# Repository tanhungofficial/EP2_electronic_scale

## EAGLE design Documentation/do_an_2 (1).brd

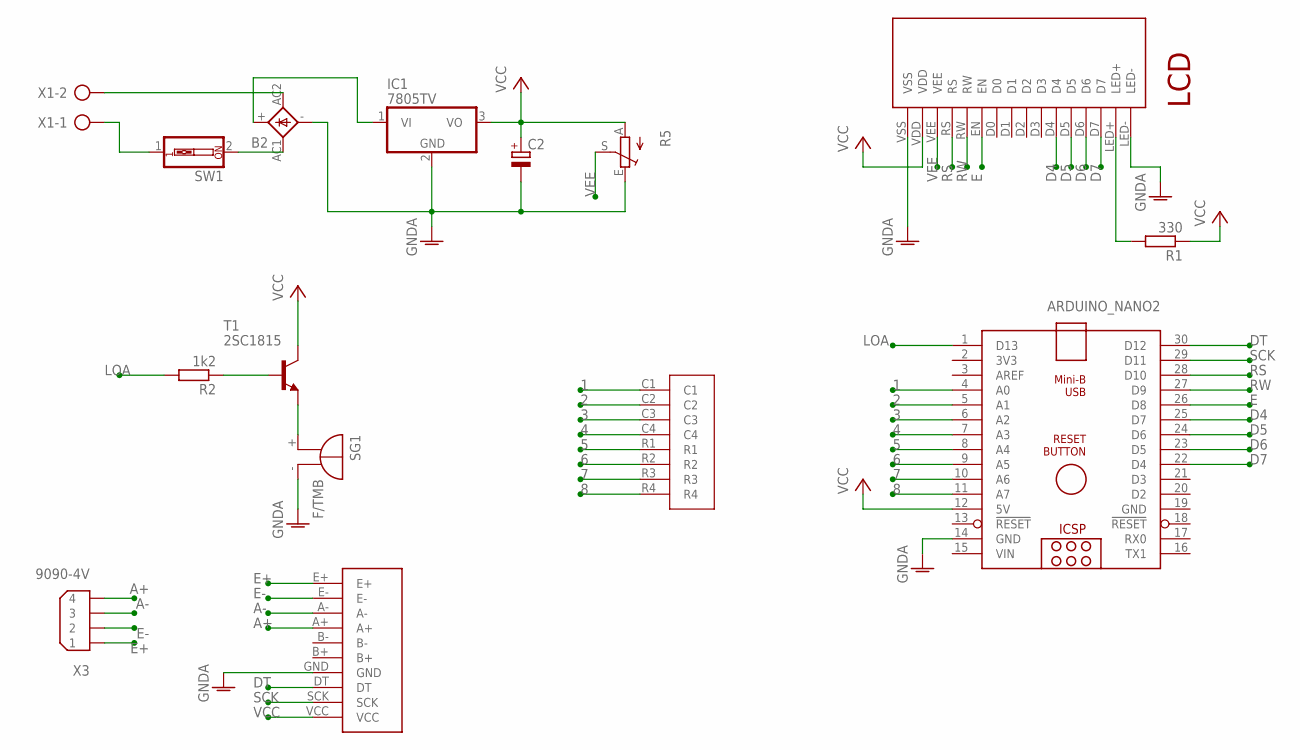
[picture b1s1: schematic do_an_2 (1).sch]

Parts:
ARDUINO_NANO2: ARDUINO_NANO
B2: 2KBP
C2: CPOL-EUE5-10.5; E5-10,5
IC1: 7805TV; TO220V
R1: 330; 0207/10
R2: 1k2; 0207/10
R5: TRIM_EU-S64W; S64W
SG1: F/TMB
SW1: SW_DIP-1; EDG-01
T1: 2SC1815; TO92-ECB
U$1: LCD20X4
U$2: MA_TRAN_PHIM
U$3: MACHMAUXANH
X1: AK300/2
X3: 9090-4V

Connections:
1: ARDUINO_NANO2.4 (A0), U$2.C1
2: ARDUINO_NANO2.5 (A1), U$2.C2
3: ARDUINO_NANO2.6 (A2), U$2.C3
4: ARDUINO_NANO2.7 (A3), U$2.C4
5: ARDUINO_NANO2.8 (A4), U$2.R1
6: ARDUINO_NANO2.9 (A5), U$2.R2
7: ARDUINO_NANO2.10 (A6), U$2.R3
8: ARDUINO_NANO2.11 (A7), U$2.R4
A+: U$3.A+, X3.4
A-: U$3.A-, X3.3
D4: ARDUINO_NANO2.25 (D7), U$1.D4
D5: ARDUINO_NANO2.24 (D6), U$1.D5
D6: ARDUINO_NANO2.23 (D5), U$1.D6
D7: ARDUINO_NANO2.22 (D4), U$1.D7
DT: ARDUINO_NANO2.30 (D12), U$3.DT
E: ARDUINO_NANO2.26 (D8), U$1.EN
E+: U$3.E+, X3.1
E-: U$3.E-, X3.2
GND: ARDUINO_NANO2.19 (GND)
GNDA: ARDUINO_NANO2.14 (GND), B2.-, C2.-, IC1.2 (GND), R5.E, SG1.-, U$1.LED-, U$1.VSS, U$3.GND
LOA: ARDUINO_NANO2.1 (D13), R2.2
unnamed: R2.1, T1.B
unnamed: B2.AC2, X1.2
unnamed: B2.AC1, SW1.2
unnamed: B2.+, IC1.1 (VI)
unnamed: R1.2, U$1.LED+
unnamed: SG1.+, T1.E
unnamed: SW1.1, X1.1
RS: ARDUINO_NANO2.28 (D10), U$1.RS
RW: ARDUINO_NANO2.27 (D9), U$1.RW
SCK: ARDUINO_NANO2.29 (D11), U$3.SCK
VCC: ARDUINO_NANO2.12 (5V), C2.+, IC1.3 (VO), R1.1, R5.A, T1.C, U$1.VDD, U$3.VCC
VEE: R5.S, U$1.VEE
VIN: ARDUINO_NANO2.15 (VIN)

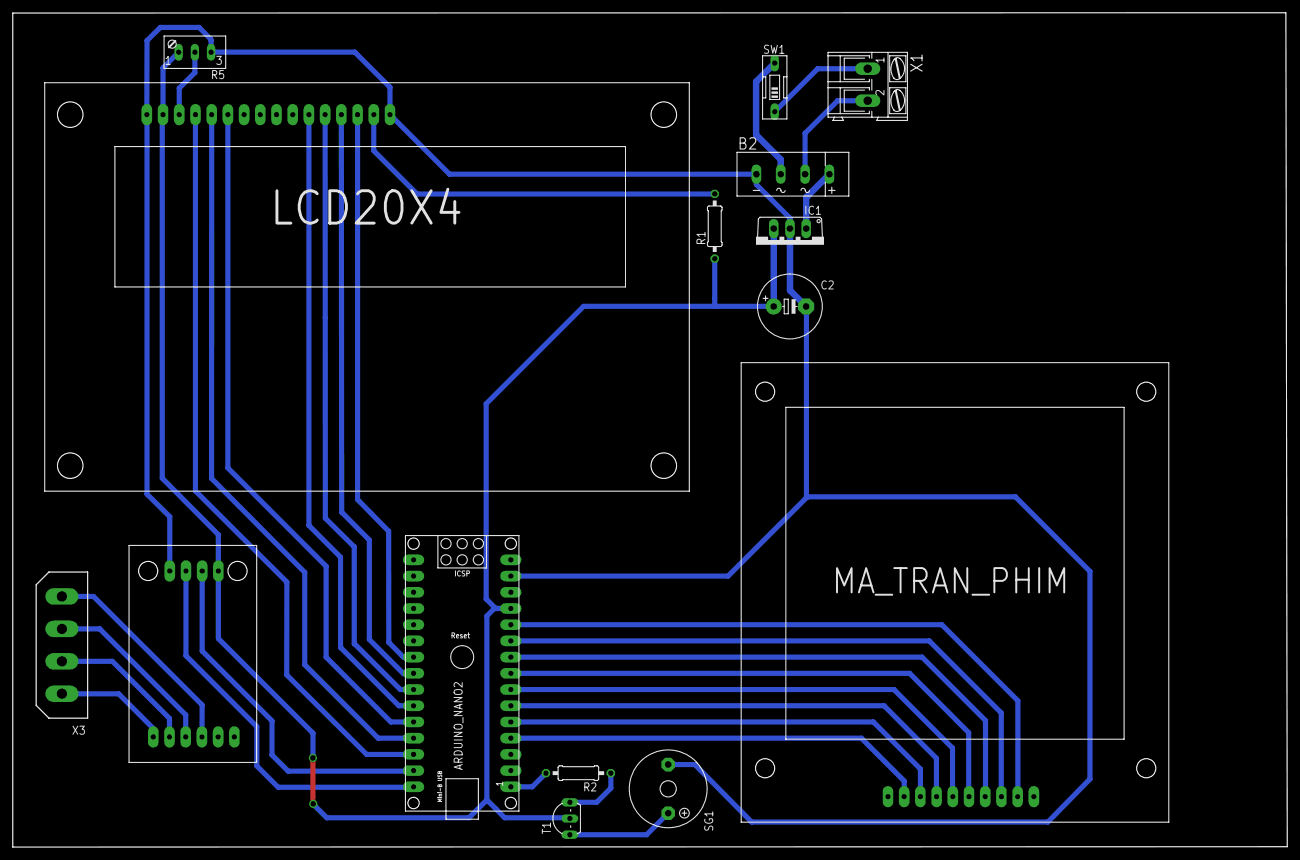
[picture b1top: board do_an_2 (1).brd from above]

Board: 2 copper layers, 199.7 x 130.7 mm, 15 parts (0 on the bottom side), 32 nets.

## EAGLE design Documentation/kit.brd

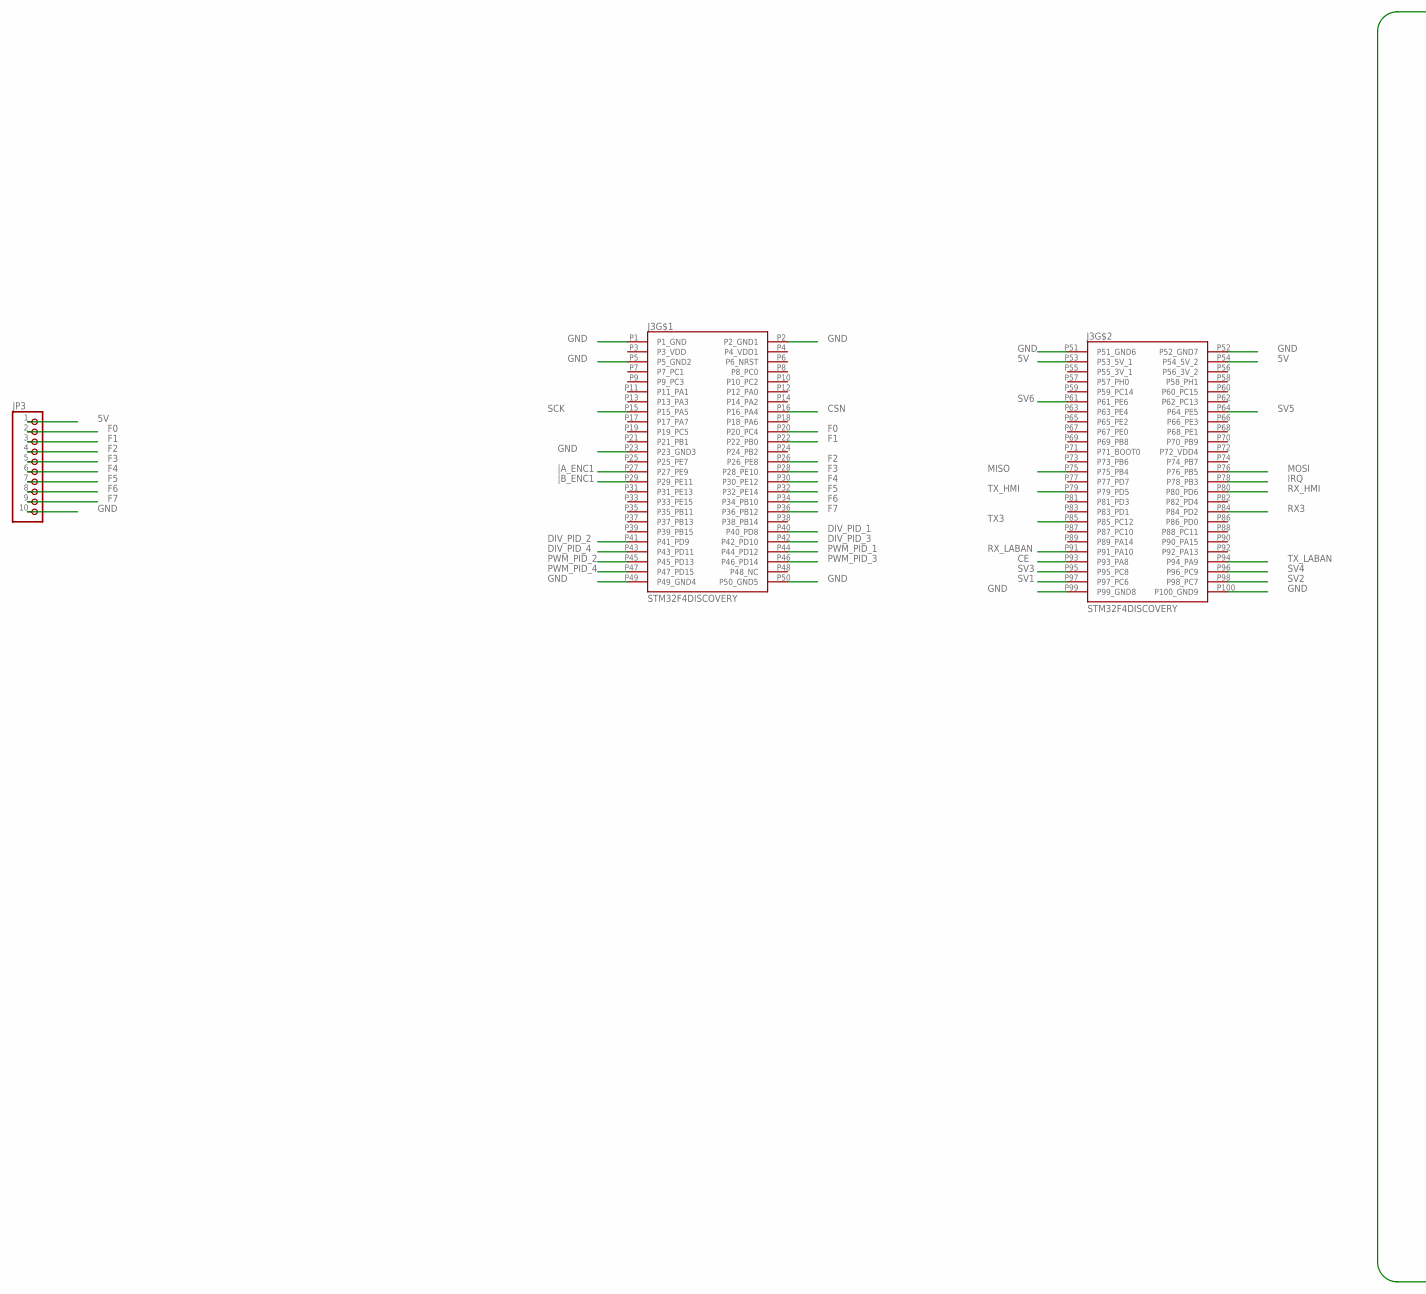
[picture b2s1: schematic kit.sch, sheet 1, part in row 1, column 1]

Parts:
J3: STM32F4DISCOVERY; STMICROELECTRONICS_STM32F4DISCOVERY
JP3: PINHD-1X10/90; 1X10/90

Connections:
5V: J3.P53 (P53_5V_1), J3.P54 (P54_5V_2), JP3.1; also elsewhere on the board
CE: J3.P93 (P93_PA8); also elsewhere on the board
CSN: J3.P16 (P16_PA4); also elsewhere on the board
DIV_PID_1: J3.P40 (P40_PD8); also elsewhere on the board
DIV_PID_2: J3.P41 (P41_PD9); also elsewhere on the board
DIV_PID_3: J3.P42 (P42_PD10); also elsewhere on the board
DIV_PID_4: J3.P43 (P43_PD11); also elsewhere on the board
F0: J3.P20 (P20_PC4), JP3.2
F1: J3.P22 (P22_PB0), JP3.3
F2: J3.P26 (P26_PE8), JP3.4
F3: J3.P28 (P28_PE10), JP3.5
F4: J3.P30 (P30_PE12), JP3.6
F5: J3.P32 (P32_PE14), JP3.7
F6: J3.P34 (P34_PB10), JP3.8
F7: J3.P36 (P36_PB12), JP3.9
GND: J3.P1 (P1_GND), J3.P2 (P2_GND1), J3.P5 (P5_GND2), J3.P23 (P23_GND3), J3.P49 (P49_GND4), J3.P50 (P50_GND5), J3.P51 (P51_GND6), J3.P52 (P52_GND7), J3.P99 (P99_GND8), J3.P100 (P100_GND9), JP3.10; also elsewhere on the board
IRQ: J3.P78 (P78_PB3); also elsewhere on the board
MISO: J3.P75 (P75_PB4); also elsewhere on the board
MOSI: J3.P76 (P76_PB5); also elsewhere on the board
PWM_PID_1: J3.P44 (P44_PD12); also elsewhere on the board
PWM_PID_2: J3.P45 (P45_PD13); also elsewhere on the board
PWM_PID_3: J3.P46 (P46_PD14); also elsewhere on the board
PWM_PID_4: J3.P47 (P47_PD15); also elsewhere on the board
RX3: J3.P84 (P84_PD2); also elsewhere on the board
RX_HMI: J3.P80 (P80_PD6)
RX_LABAN: J3.P91 (P91_PA10); also elsewhere on the board
SCK: J3.P15 (P15_PA5); also elsewhere on the board
SV1: J3.P97 (P97_PC6); also elsewhere on the board
SV2: J3.P98 (P98_PC7); also elsewhere on the board
SV3: J3.P95 (P95_PC8); also elsewhere on the board
SV4: J3.P96 (P96_PC9); also elsewhere on the board
SV5: J3.P64 (P64_PE5)
SV6: J3.P61 (P61_PE6)
TX3: J3.P85 (P85_PC12); also elsewhere on the board
TX_HMI: J3.P79 (P79_PD5)
TX_LABAN: J3.P94 (P94_PA9); also elsewhere on the board
|A_ENC1: J3.P27 (P27_PE9); also elsewhere on the board
|B_ENC1: J3.P29 (P29_PE11); also elsewhere on the board

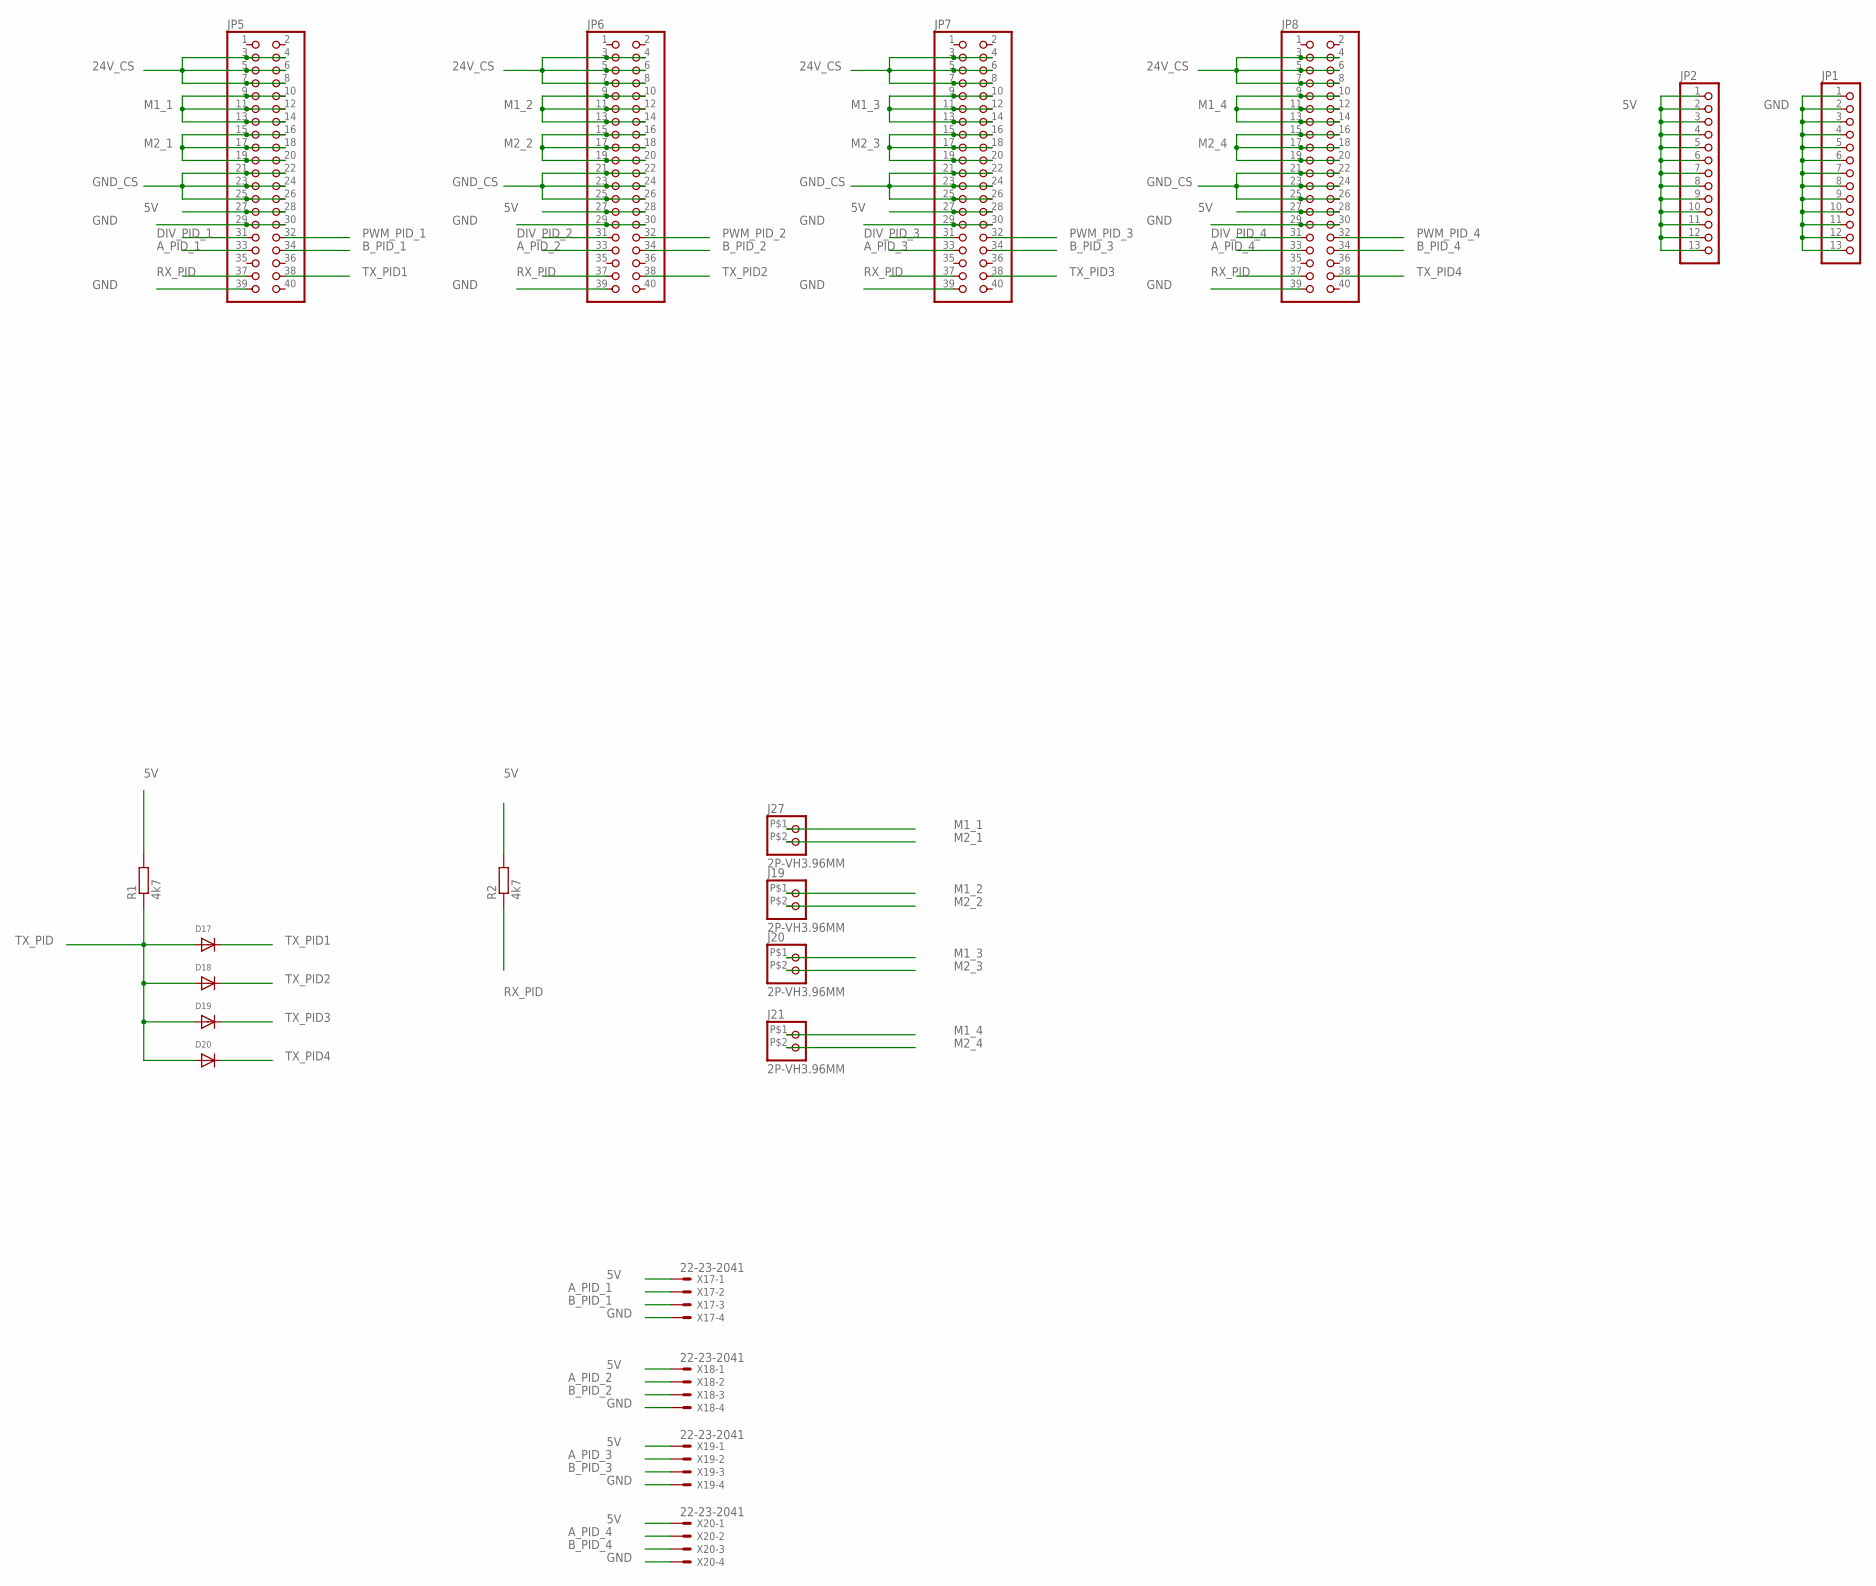
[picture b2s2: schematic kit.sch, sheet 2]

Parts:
D17, D18, D19, D20: DIODEDO-1N4148; DO-1N4148
J19, J20, J21, J27: 2P-VH3.96MM
JP1, JP2: PINHD-1X13; 1X13
JP5, JP6, JP7, JP8: PINHD-2X20; 2X20
R1, R2: 4k7; 0207/10
X17, X18, X19, X20: 22-23-2041

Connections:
5V: JP2.1, JP2.2, JP2.3, JP2.4, JP2.5, JP2.6, JP2.7, JP2.8, JP2.9, JP2.10, JP2.11, JP2.12, JP2.13, JP5.27, JP5.28, JP6.27, JP6.28, JP7.27, JP7.28, JP8.27, JP8.28, R1.2, R2.2, X17.1, X18.1, X19.1, X20.1; also elsewhere on the board
24V_CS: JP5.3, JP5.4, JP5.5, JP5.6, JP5.7, JP5.8, JP6.3, JP6.4, JP6.5, JP6.6, JP6.7, JP6.8, JP7.3, JP7.4, JP7.5, JP7.6, JP7.7, JP7.8, JP8.3, JP8.4, JP8.5, JP8.6, JP8.7, JP8.8; also elsewhere on the board
A_PID_1: JP5.33, X17.2
A_PID_2: JP6.33, X18.2
A_PID_3: JP7.33, X19.2
A_PID_4: JP8.33, X20.2
B_PID_1: JP5.34, X17.3
B_PID_2: JP6.34, X18.3
B_PID_3: JP7.34, X19.3
B_PID_4: JP8.34, X20.3
DIV_PID_1: JP5.31; also elsewhere on the board
DIV_PID_2: JP6.31; also elsewhere on the board
DIV_PID_3: JP7.31; also elsewhere on the board
DIV_PID_4: JP8.31; also elsewhere on the board
GND: JP1.1, JP1.2, JP1.3, JP1.4, JP1.5, JP1.6, JP1.7, JP1.8, JP1.9, JP1.10, JP1.11, JP1.12, JP1.13, JP5.29, JP5.30, JP5.39, JP6.29, JP6.30, JP6.39, JP7.29, JP7.30, JP7.39, JP8.29, JP8.30, JP8.39, X17.4, X18.4, X19.4, X20.4; also elsewhere on the board
GND_CS: JP5.21, JP5.22, JP5.23, JP5.24, JP5.25, JP5.26, JP6.21, JP6.22, JP6.23, JP6.24, JP6.25, JP6.26, JP7.21, JP7.22, JP7.23, JP7.24, JP7.25, JP7.26, JP8.21, JP8.22, JP8.23, JP8.24, JP8.25, JP8.26; also elsewhere on the board
M1_1: J27.P$1 (1), JP5.9, JP5.10, JP5.11, JP5.12, JP5.13, JP5.14
M1_2: J19.P$1 (1), JP6.9, JP6.10, JP6.11, JP6.12, JP6.13, JP6.14
M1_3: J20.P$1 (1), JP7.9, JP7.10, JP7.11, JP7.12, JP7.13, JP7.14
M1_4: J21.P$1 (1), JP8.9, JP8.10, JP8.11, JP8.12, JP8.13, JP8.14
M2_1: J27.P$2 (2), JP5.15, JP5.16, JP5.17, JP5.18, JP5.19, JP5.20
M2_2: J19.P$2 (2), JP6.15, JP6.16, JP6.17, JP6.18, JP6.19, JP6.20
M2_3: J20.P$2 (2), JP7.15, JP7.16, JP7.17, JP7.18, JP7.19, JP7.20
M2_4: J21.P$2 (2), JP8.15, JP8.16, JP8.17, JP8.18, JP8.19, JP8.20
PWM_PID_1: JP5.32; also elsewhere on the board
PWM_PID_2: JP6.32; also elsewhere on the board
PWM_PID_3: JP7.32; also elsewhere on the board
PWM_PID_4: JP8.32; also elsewhere on the board
RX_PID: JP5.37, JP6.37, JP7.37, JP8.37, R2.1; also elsewhere on the board
TX_PID: D17.A, D18.A, D19.A, D20.A, R1.1; also elsewhere on the board
TX_PID1: D17.C, JP5.38
TX_PID2: D18.C, JP6.38
TX_PID3: D19.C, JP7.38
TX_PID4: D20.C, JP8.38

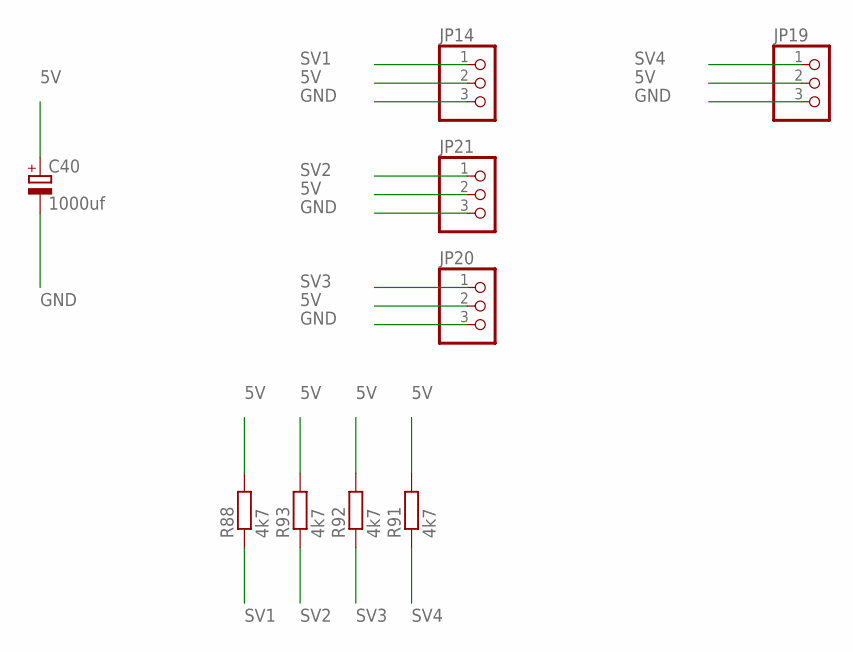
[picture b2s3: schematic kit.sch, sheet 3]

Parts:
C40: 1000uf; E5-10,5
JP14, JP19, JP20, JP21: PINHD-1X3; 1X03
R88, R91, R92, R93: 4k7; 0207/10

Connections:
5V: C40.+, JP14.2, JP19.2, JP20.2, JP21.2, R88.2, R91.2, R92.2, R93.2; also elsewhere on the board
GND: C40.-, JP14.3, JP19.3, JP20.3, JP21.3; also elsewhere on the board
SV1: JP14.1, R88.1; also elsewhere on the board
SV2: JP21.1, R93.1; also elsewhere on the board
SV3: JP20.1, R92.1; also elsewhere on the board
SV4: JP19.1, R91.1; also elsewhere on the board

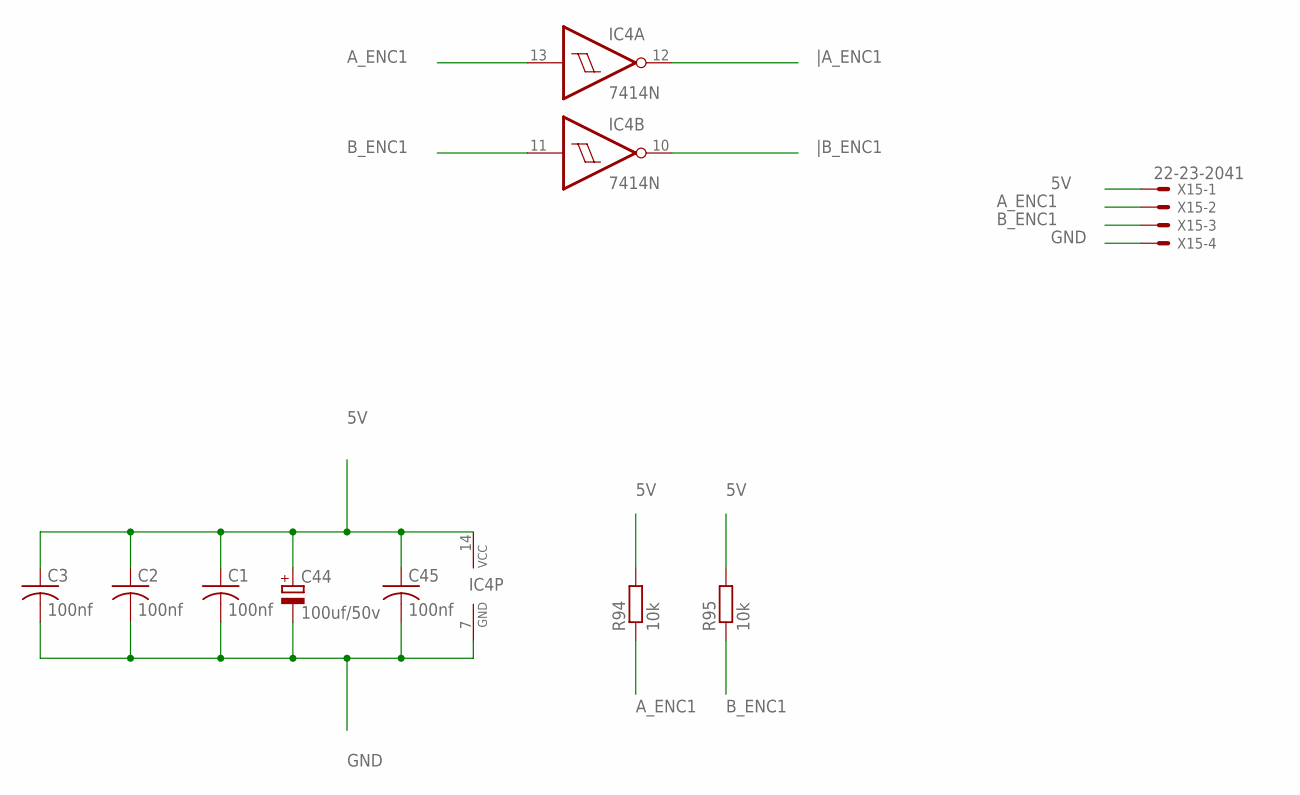
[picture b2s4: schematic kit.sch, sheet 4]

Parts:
C1, C2, C3, C45: 100nf; C050-025X075
C44: 100uf/50v; E5-10,5
IC4: 7414N; DIL14
R94, R95: 10k; 0207/10
X15: 22-23-2041

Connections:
5V: C1.1, C2.1, C3.1, C44.+, C45.1, IC4.14 (VCC), R94.2, R95.2, X15.1; also elsewhere on the board
A_ENC1: IC4.13 (I), R94.1, X15.2
B_ENC1: IC4.11 (I), R95.1, X15.3
GND: C1.2, C2.2, C3.2, C44.-, C45.2, IC4.7 (GND), X15.4; also elsewhere on the board
|A_ENC1: IC4.12 (O); also elsewhere on the board
|B_ENC1: IC4.10 (O); also elsewhere on the board

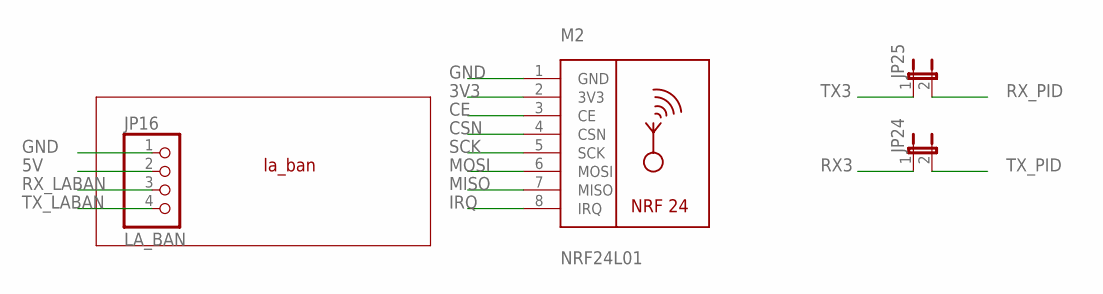
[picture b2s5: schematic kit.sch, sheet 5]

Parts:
JP16: LA_BAN; 1X04
JP24, JP25: JP1E; JP1
M2: NRF24L01; NRF24L01_CHANCAM_ANTEN_ONBOARD

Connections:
3V3: M2.2 (3V3); also elsewhere on the board
5V: JP16.2; also elsewhere on the board
CE: M2.3 (CE); also elsewhere on the board
CSN: M2.4 (CSN); also elsewhere on the board
GND: JP16.1, M2.1 (GND); also elsewhere on the board
IRQ: M2.8 (IRQ); also elsewhere on the board
MISO: M2.7 (MISO); also elsewhere on the board
MOSI: M2.6 (MOSI); also elsewhere on the board
RX3: JP24.1; also elsewhere on the board
RX_LABAN: JP16.3; also elsewhere on the board
RX_PID: JP25.2; also elsewhere on the board
SCK: M2.5 (SCK); also elsewhere on the board
TX3: JP25.1; also elsewhere on the board
TX_LABAN: JP16.4; also elsewhere on the board
TX_PID: JP24.2; also elsewhere on the board

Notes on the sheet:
la_ban

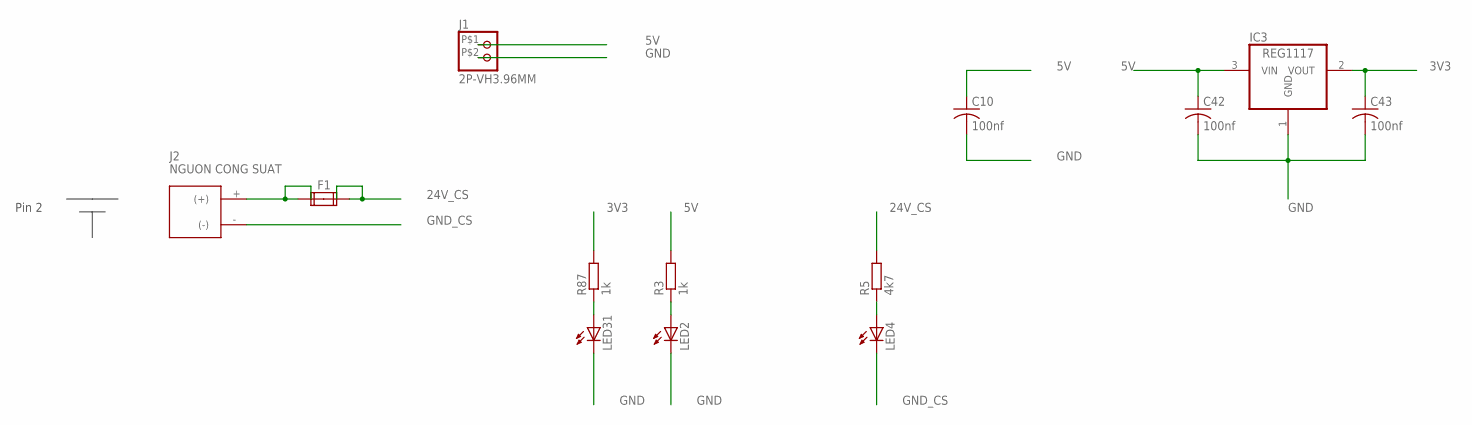
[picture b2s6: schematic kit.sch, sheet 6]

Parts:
C10, C42, C43: 100nf; C050-025X075
F1: FUSE2P; FUSE1
IC3: REG1117; SOT223
J1: 2P-VH3.96MM
J2: NGUON CONG SUAT; XT-60
LED2, LED4, LED31: LED3MM
R3, R87: 1k; 0207/10
R5: 4k7; 0207/10

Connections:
3V3: C43.1, IC3.2 (VOUT), R87.2; also elsewhere on the board
5V: C10.1, C42.1, IC3.3 (VIN), J1.P$1 (1), R3.2; also elsewhere on the board
24V_CS: F1.2A, F1.2B, R5.2; also elsewhere on the board
GND: C10.2, C42.2, C43.2, IC3.1 (GND), J1.P$2 (2), LED2.K (C), LED31.K (C); also elsewhere on the board
GND_CS: J2.- ((-)), LED4.K (C); also elsewhere on the board
unnamed: LED2.A, R3.1
unnamed: LED4.A, R5.1
unnamed: F1.1A, F1.1B, J2.+ ((+))
unnamed: LED31.A, R87.1

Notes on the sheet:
Pin 2

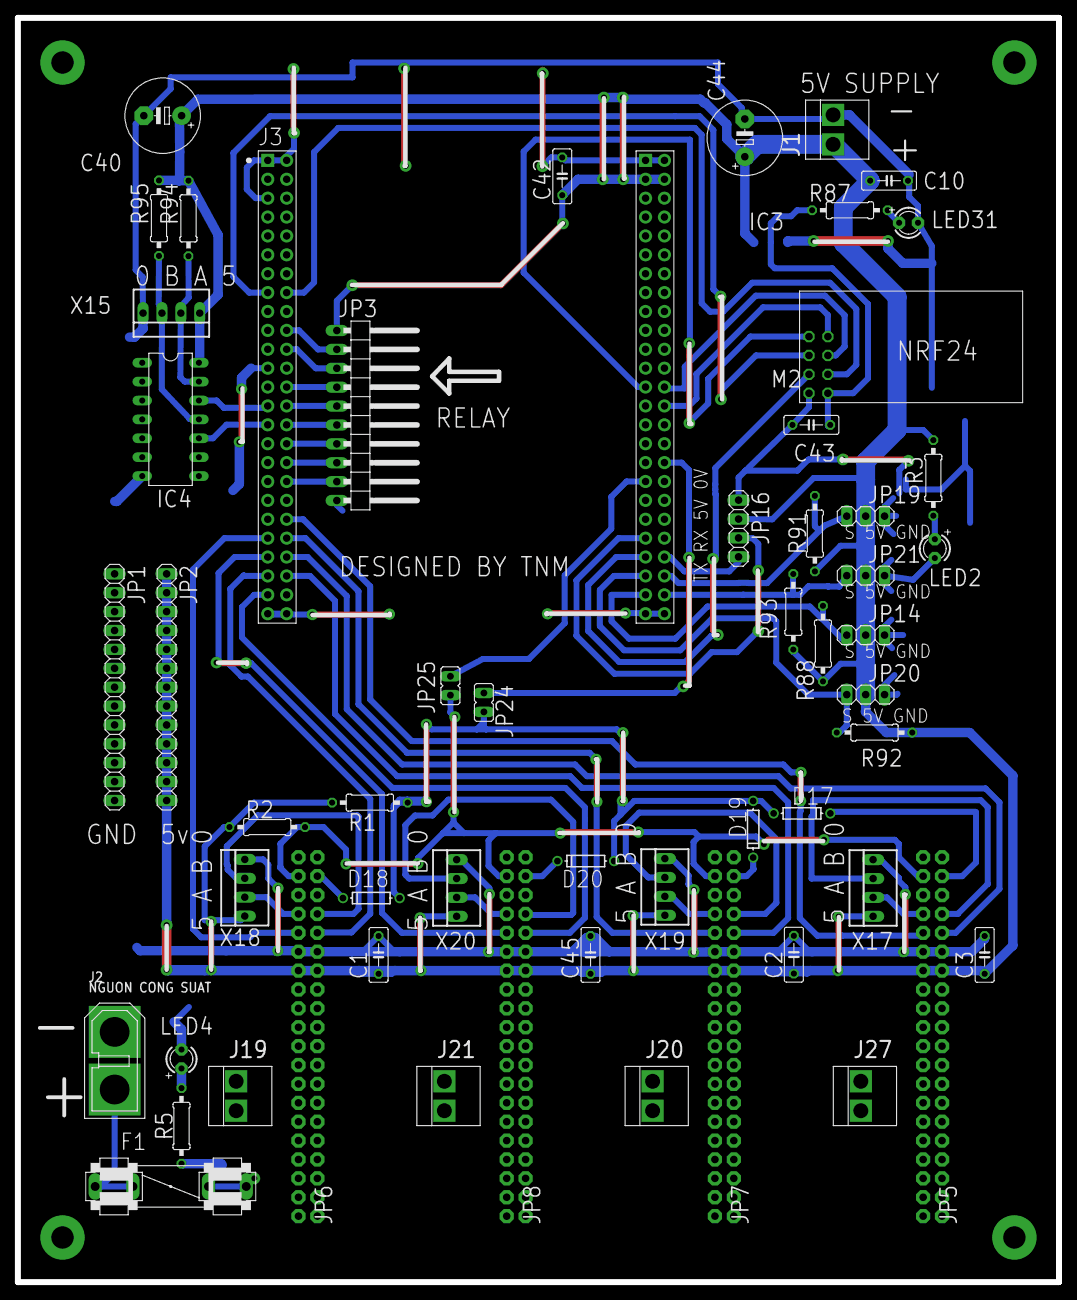
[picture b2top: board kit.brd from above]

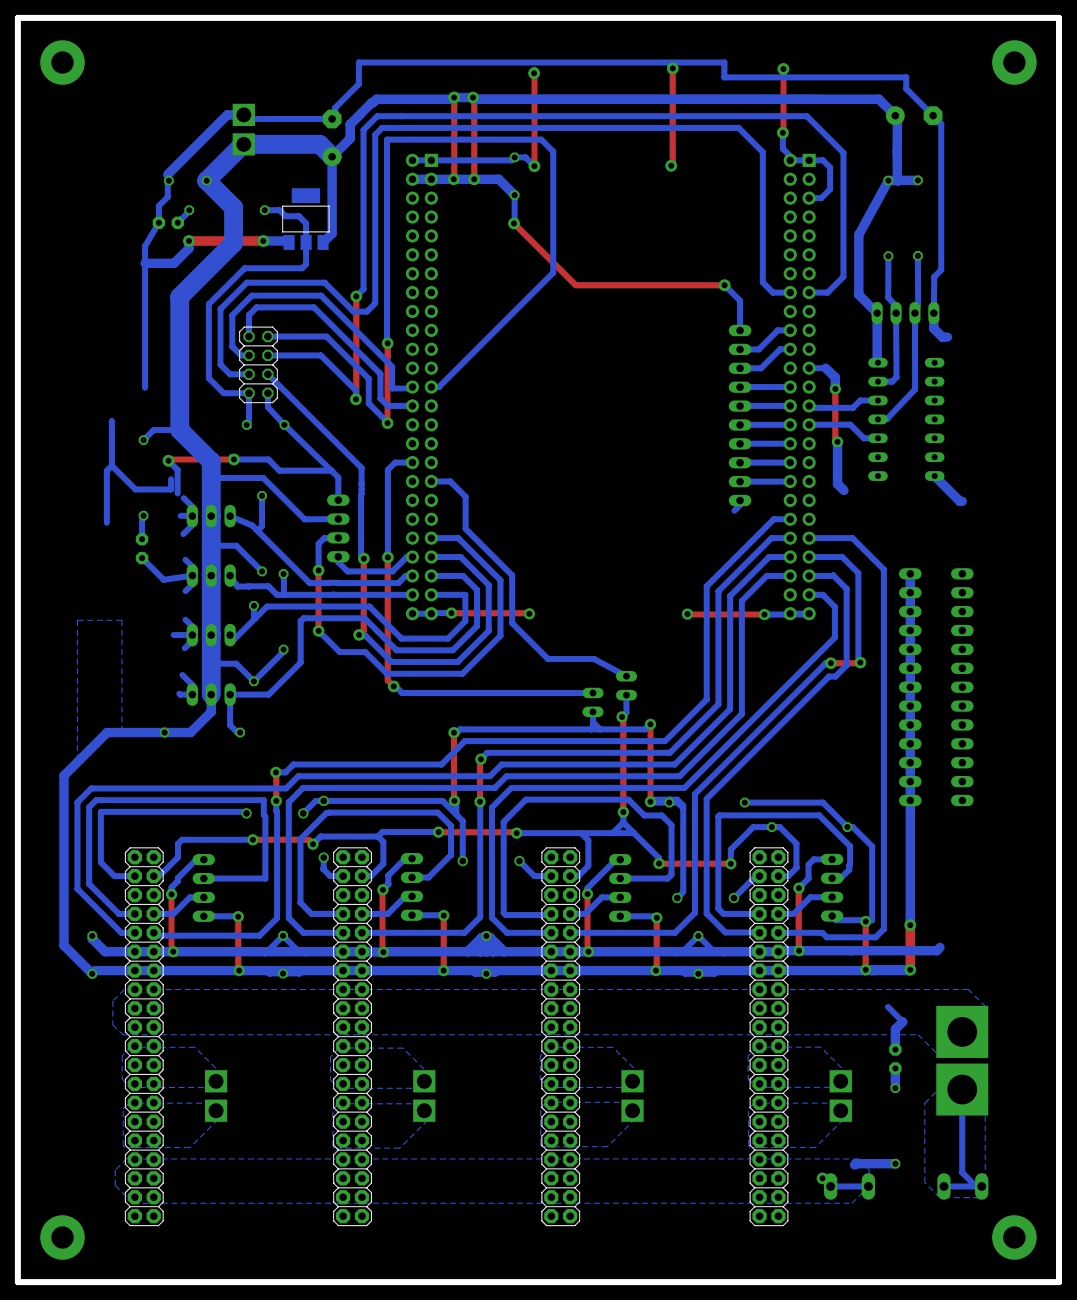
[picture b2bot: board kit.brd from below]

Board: 2 copper layers, 140.0 x 170.0 mm, 57 parts (5 on the bottom side), 65 nets.

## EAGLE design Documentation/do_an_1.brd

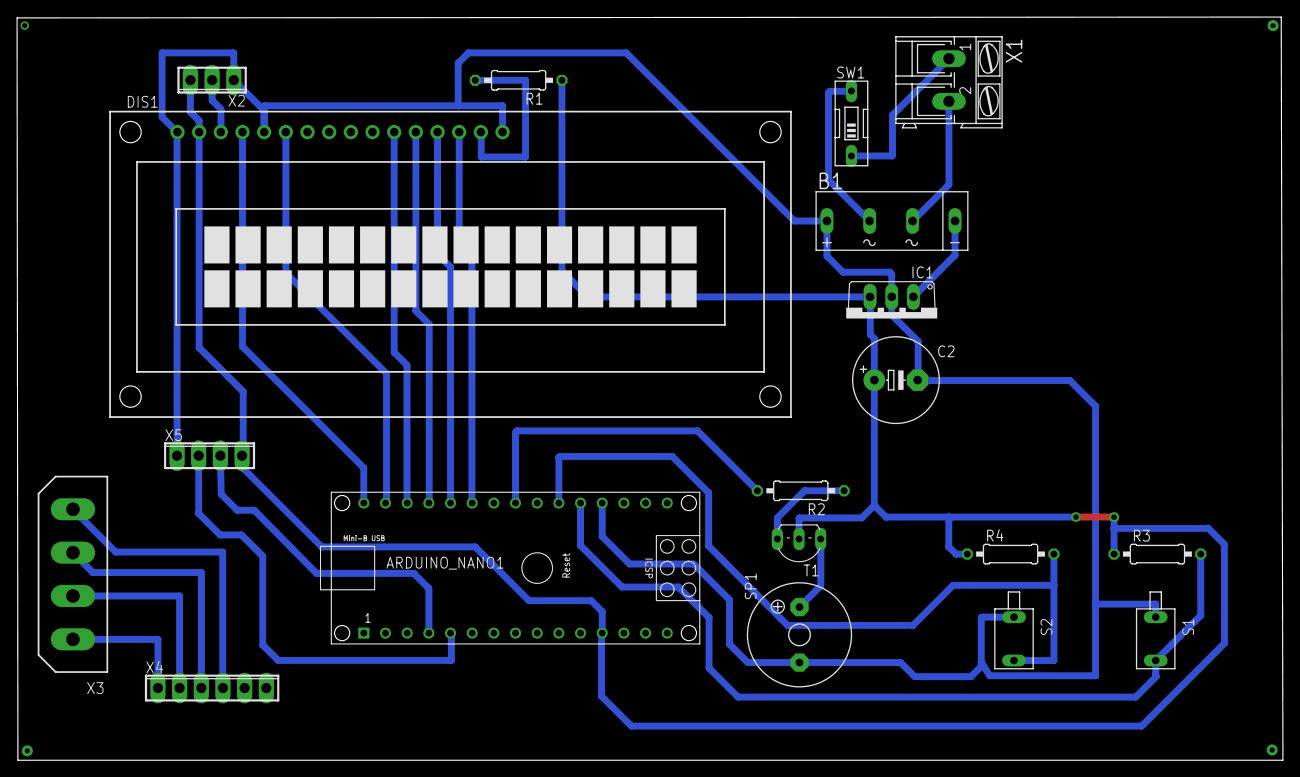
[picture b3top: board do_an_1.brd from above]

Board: 2 copper layers, 148.4 x 87.1 mm, 19 parts (0 on the bottom side), 25 nets.

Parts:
ARDUINO_NANO1: ARDUINO_NANO
B1: 2KBB-R
C2: E5-10,5
DIS1: TUXGR_16X2_R2
IC1: 7805TV; TO220V
R1: 330; 0207/10
R2: 1k2; 0207/10
R3, R4: 10k; 0207/10
S1, S2: GF11MCBE; GP11MCBE
SP1: KSS1201
SW1: EDG-01
T1: 2SC1815; TO92-ECB
X1: AK300/2
X2: 3POL254
X3: 9090-4V
X4: 6POL254
X5: 4POL254

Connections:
A0: ARDUINO_NANO1.4, X5.3
A1: ARDUINO_NANO1.5, X5.2
BT1: ARDUINO_NANO1.20, R3.2, S1.3
BT2: ARDUINO_NANO1.21, R4.2, S2.3
D4: ARDUINO_NANO1.28, DIS1.11
D5: ARDUINO_NANO1.27, DIS1.12
D6: ARDUINO_NANO1.26, DIS1.13
D7: ARDUINO_NANO1.25, DIS1.14
E: ARDUINO_NANO1.29, DIS1.6
GNDA: ARDUINO_NANO1.19, B1.+, C2.-, DIS1.1, DIS1.5, DIS1.16, IC1.2, S1.1, S2.1, SP1.-, X2.1, X5.1
LOA: ARDUINO_NANO1.23, R2.2
unnamed: R2.1, T1.B
unnamed: B1.AC1, SW1.2
unnamed: B1.AC2, X1.2
unnamed: B1.-, IC1.1
unnamed: DIS1.3, X2.2
unnamed: DIS1.15, R1.2
unnamed: X3.1, X4.1
unnamed: X3.2, X4.2
unnamed: SP1.+, T1.E
unnamed: X3.3, X4.3
unnamed: X3.4, X4.4
unnamed: SW1.1, X1.1
RS: ARDUINO_NANO1.30, DIS1.4
VCC: ARDUINO_NANO1.12, C2.+, DIS1.2, IC1.3, R1.1, R3.1, R4.1, T1.C, X2.3, X5.4

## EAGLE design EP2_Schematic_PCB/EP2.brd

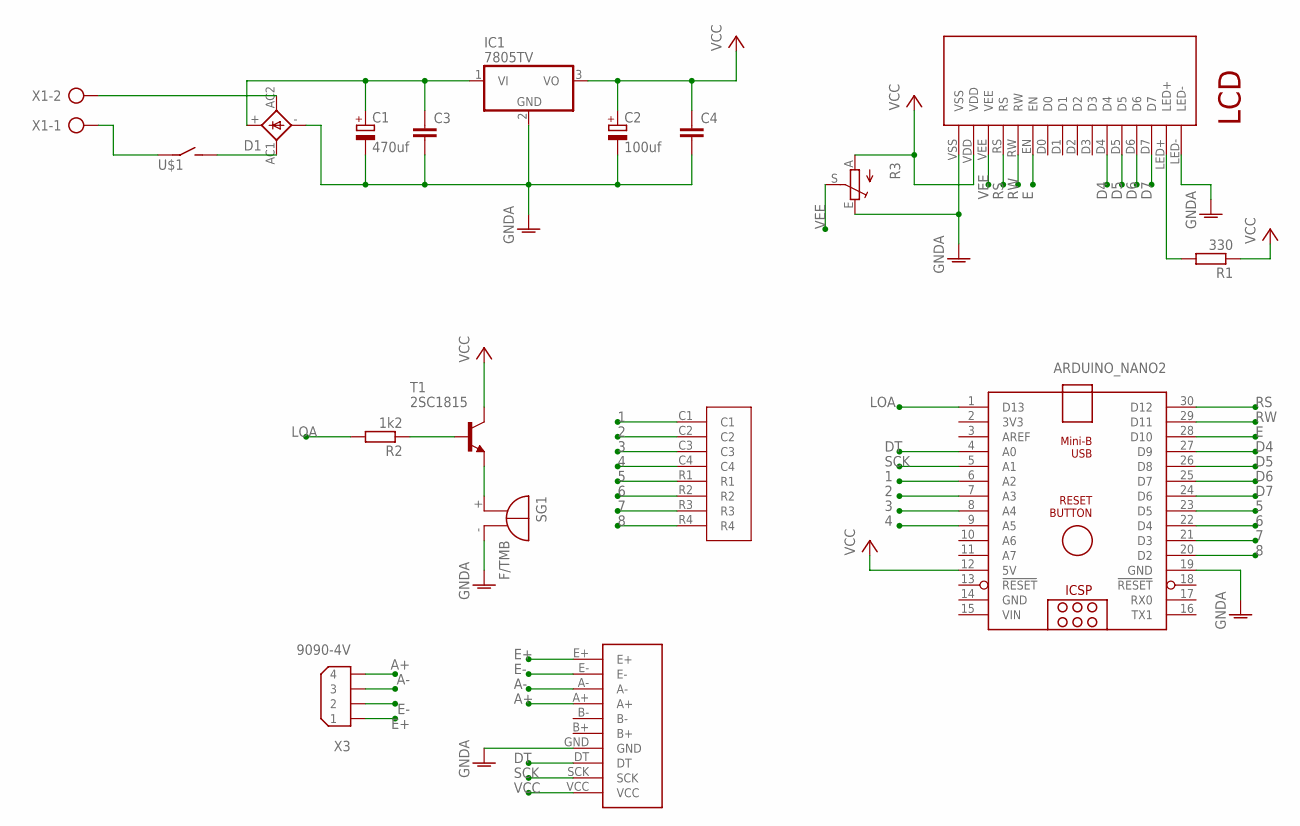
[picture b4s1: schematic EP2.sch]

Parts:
ARDUINO_NANO2: ARDUINO_NANO
C1: 470uf; E3,5-8
C2: 100uf; E2-5
C3, C4: C-EU025-024X044; C025-024X044
D1: 2KBP
IC1: 7805TV; TO220V
LCD: LCD20X4
M1: MACHMAUXANH
R1: 330; 0207/10
R2: 1k2; 0207/10
R3: TRIM_EU-S64W; S64W
SG1: F/TMB
T1: 2SC1815; TO92-ECB
U$1: CONG_TAC
U$2: MA_TRAN_PHIM
X1: AK300/2
X3: 9090-4V

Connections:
1: ARDUINO_NANO2.6 (A2), U$2.C1
2: ARDUINO_NANO2.7 (A3), U$2.C2
3: ARDUINO_NANO2.8 (A4), U$2.C3
4: ARDUINO_NANO2.9 (A5), U$2.C4
5: ARDUINO_NANO2.23 (D5), U$2.R1
6: ARDUINO_NANO2.22 (D4), U$2.R2
7: ARDUINO_NANO2.21 (D3), U$2.R3
8: ARDUINO_NANO2.20 (D2), U$2.R4
A+: M1.A+, X3.4
A-: M1.A-, X3.3
D4: ARDUINO_NANO2.27 (D9), LCD.D4
D5: ARDUINO_NANO2.26 (D8), LCD.D5
D6: ARDUINO_NANO2.25 (D7), LCD.D6
D7: ARDUINO_NANO2.24 (D6), LCD.D7
DT: ARDUINO_NANO2.4 (A0), M1.DT
E: ARDUINO_NANO2.28 (D10), LCD.EN
E+: M1.E+, X3.1
E-: M1.E-, X3.2
GND: ARDUINO_NANO2.14 (GND)
GNDA: ARDUINO_NANO2.19 (GND), C1.-, C2.-, C3.2, C4.2, D1.-, IC1.2 (GND), LCD.LED-, LCD.VSS, M1.GND, R3.E, SG1.-
LOA: ARDUINO_NANO2.1 (D13), R2.2
unnamed: R2.1, T1.B
unnamed: D1.AC2, X1.2
unnamed: D1.AC1, U$1.P$2 (2)
unnamed: C1.+, C3.1, D1.+, IC1.1 (VI)
unnamed: LCD.LED+, R1.2
unnamed: SG1.+, T1.E
unnamed: U$1.P$1 (1), X1.1
RS: ARDUINO_NANO2.30 (D12), LCD.RS
RW: ARDUINO_NANO2.29 (D11), LCD.RW
SCK: ARDUINO_NANO2.5 (A1), M1.SCK
VCC: ARDUINO_NANO2.12 (5V), C2.+, C4.1, IC1.3 (VO), LCD.VDD, M1.VCC, R1.1, R3.A, T1.C
VEE: LCD.VEE, R3.S
VIN: ARDUINO_NANO2.15 (VIN)

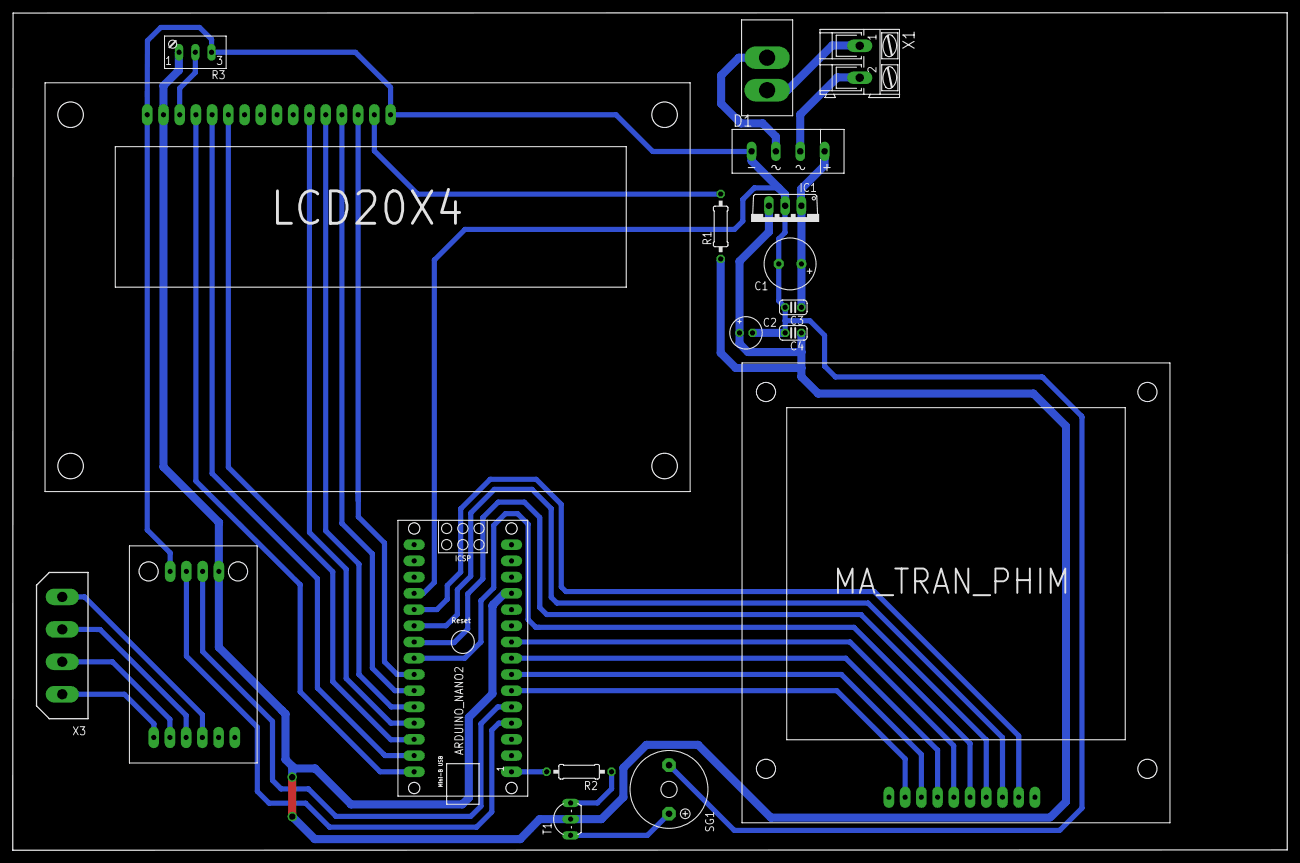
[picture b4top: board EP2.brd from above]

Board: 2 copper layers, 199.5 x 131.1 mm, 18 parts (0 on the bottom side), 32 nets.

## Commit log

2019-12-12 the first
2019-12-12 the second
2019-12-27 complete
